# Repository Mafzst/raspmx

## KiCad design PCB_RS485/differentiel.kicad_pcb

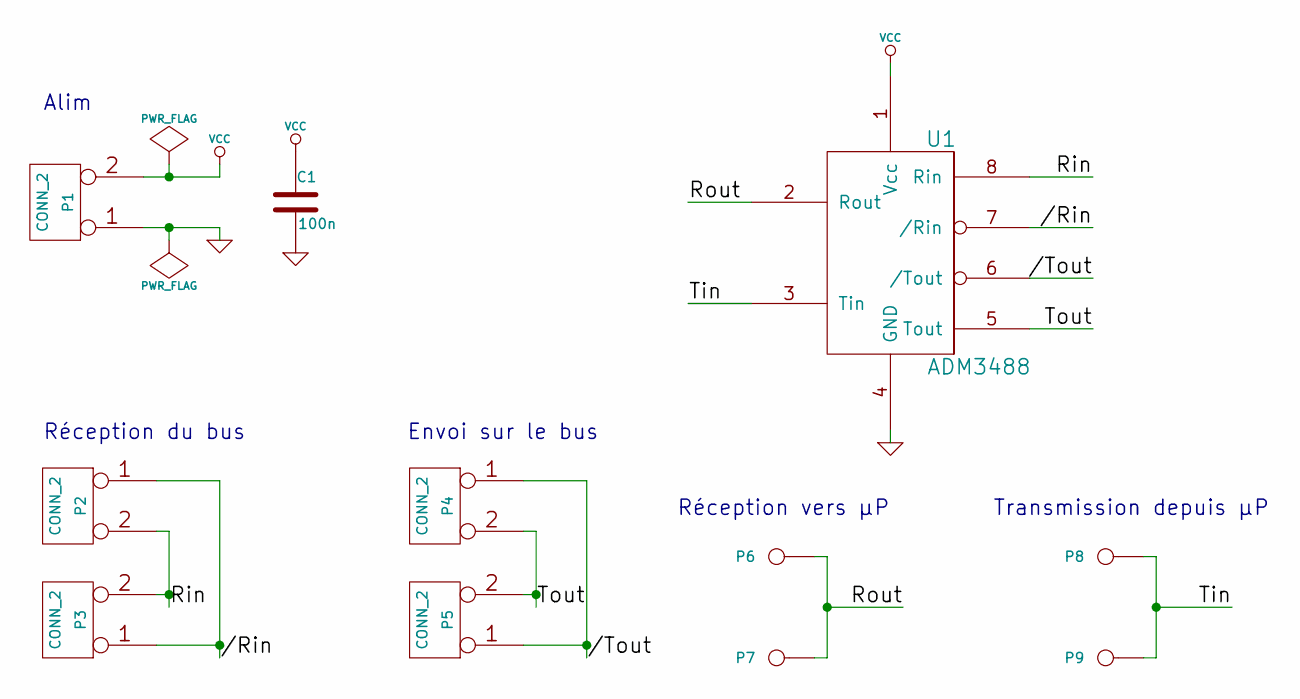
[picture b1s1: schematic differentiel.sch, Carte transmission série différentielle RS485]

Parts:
C1: 100n
P1, P2, P3, P4, P5: CONN_2
P6, P7, P8, P9: CONN_1
U1: ADM3488

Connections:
//Rin: P2.1, P3.1, U1.7 (/Rin)
//Tout: P4.1, P5.1, U1.6 (/Tout)
/Rin: P2.2 (PM), P3.2 (PM), U1.8 (Rin)
/Rout: P6.1, P7.1, U1.2 (Rout)
/Tin: P8.1, P9.1, U1.3 (Tin)
/Tout: P4.2 (PM), P5.2 (PM), U1.5 (Tout)
GND: C1.2, P1.1, U1.4 (GND)
VCC: C1.1, P1.2 (PM), U1.1 (Vcc)

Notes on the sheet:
Alim
Réception du bus
Envoi sur le bus
Réception vers µP
Transmission depuis µP

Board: 2 copper layers, 11 parts (0 on the bottom side), 8 nets, no tracks yet.

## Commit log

2017-09-17 Raspberry code
2017-09-17 Arduino V1
2017-09-17 Arduino V2
2017-09-17 Arduino V3
2017-09-17 Arduino V4
2017-09-17 RS485 PCB
2017-09-17 Licencing
